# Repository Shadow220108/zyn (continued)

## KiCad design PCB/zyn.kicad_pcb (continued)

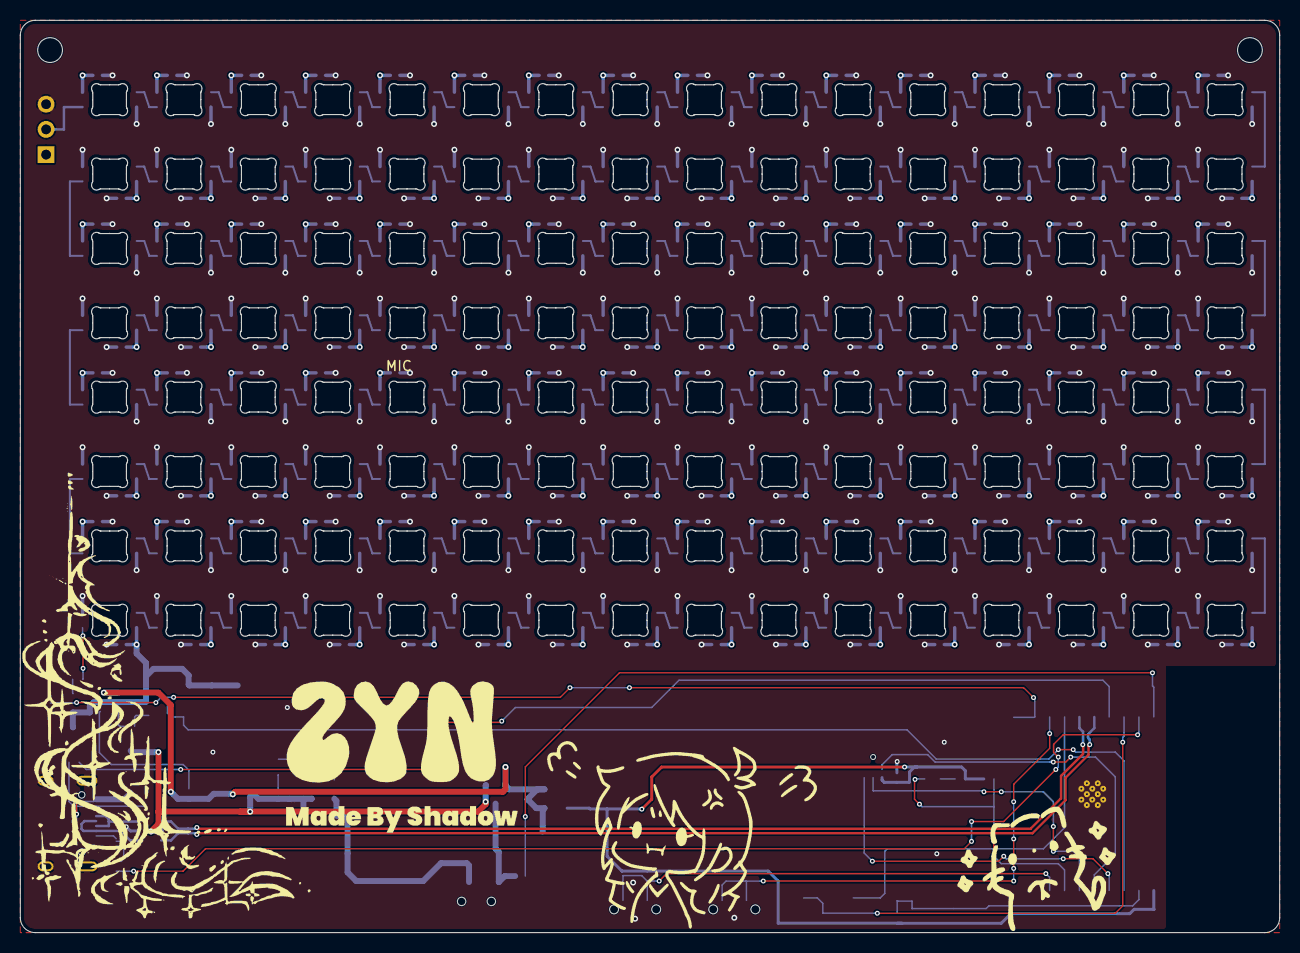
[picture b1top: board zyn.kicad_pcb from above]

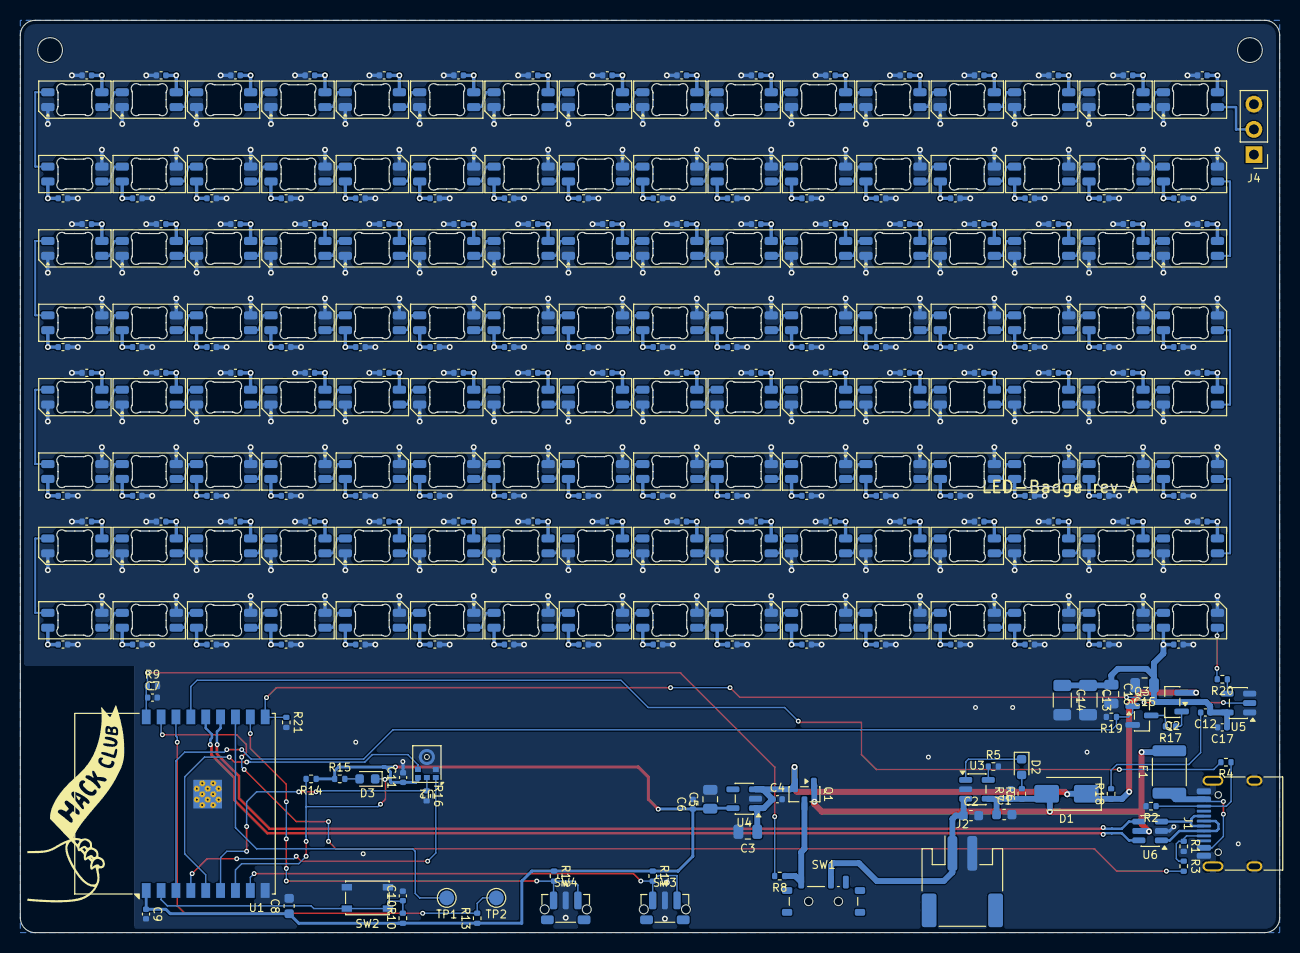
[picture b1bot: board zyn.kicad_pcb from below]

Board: 4 copper layers, 127.0 x 92.0 mm, 318 parts (316 on the bottom side), 165 nets.

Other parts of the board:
H1, H2: MountingHole_2.5mm

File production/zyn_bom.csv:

Designator,Footprint,Quantity,Value,LCSC Part #
"C1, C2",0603,2,4.7u/10V,CL10A475KO8NNNC
"C10, C4, C6",0402,3,1u/10V,CL05A105KP5NNNC
"C101, C102, C103, C104, C105, C106, C107, C108, C109, C11, C110, C111, C112, C113, C114, C115, C116, C117, C118, C119, C120, C121, C122, C123, C124, C125, C126, C127, C128, C129, C130, C131, C132, C133, C134, C135, C136, C137, C138, C139, C140, C141, C142, C143, C144, C145, C146, C147, C148, C149, C150, C151, C152, C153, C154, C155, C156, C157, C158, C159, C160, C161, C162, C163, C164, C165, C166, C167, C168, C169, C17, C170, C171, C172, C173, C174, C175, C176, C177, C178, C179, C180, C181, C182, C183, C184, C185, C186, C187, C188, C189, C190, C191, C192, C193, C194, C195, C196, C197, C198, C199, C200, C201, C202, C203, C204, C205, C206, C207, C208, C209, C210, C211, C212, C213, C214, C215, C216, C217, C218, C219, C220, C221, C222, C223, C224, C225, C226, C227, C228, C7, C9",0402,132,100n/16V,CL05B104KO5NNNC
C12,0402,1,47n/16V,CL05B473KO5NNNC
"C13, C14",1206,2,47u/10V,CL31A476MPHNNNE
"C15, C16, C3, C5",0805,4,22u/10V,CL21A226MPQNNNE
C8,0603,1,10u/10V,CL10A106KP8NNNC
D1,D_SMA,1,SS34,SS34 (3 A / 40 V)
"D101, D102, D103, D104, D105, D106, D107, D108, D109, D110, D111, D112, D113, D114, D115, D116, D117, D118, D119, D120, D121, D122, D123, D124, D125, D126, D127, D128, D129, D130, D131, D132, D133, D134, D135, D136, D137, D138, D139, D140, D141, D142, D143, D144, D145, D146, D147, D148, D149, D150, D151, D152, D153, D154, D155, D156, D157, D158, D159, D160, D161, D162, D163, D164, D165, D166, D167, D168, D169, D170, D171, D172, D173, D174, D175, D176, D177, D178, D179, D180, D181, D182, D183, D184, D185, D186, D187, D188, D189, D190, D191, D192, D193, D194, D195, D196, D197, D198, D199, D200, D201, D202, D203, D204, D205, D206, D207, D208, D209, D210, D211, D212, D213, D214, D215, D216, D217, D218, D219, D220, D221, D222, D223, D224, D225, D226, D227, D228",LED_SK6812MINI-E_3.2x2.8mm_P1.5mm_ReverseMount,128,SK6812MINI-E,SK6812MINI-E
D2,0603,1,RED (charging),KT-0603R
D3,0603,1,BLUE (IO8),KT-0603B
F1,1812,1,2A,"Bourns MF-MSMF200-2 (1812, 2 A hold)"
J1,USB_C_Receptacle_HRO_TYPE-C-31-M-12,1,USB-C,HRO TYPE-C-31-M-12
J2,JST_PH_S2B-PH-SM4-TB_1x02-1MP_P2.00mm_Horizontal,1,LiPo 1S (JST-PH),JST S2B-PH-SM4-TB
J4,PinHeader_1x03_P2.54mm_Vertical,1,CHAIN OUT,2.54 mm 1x3 header (DNP)
"Q1, Q2",SOT-23,2,AO3401A,AO3401A
Q3,SOT-23,1,2N7002,2N7002
"R1, R2",0402,2,5.1k,RC0402FR-075K1L
"R10, R11, R12, R13, R14, R17, R3, R4",0402,8,10k,RC0402FR-0710KL
"R15, R6",0402,2,1k,RC0402FR-071KL
"R16, R18, R19, R21, R7, R8, R9",0402,7,100k,RC0402FR-07100KL
R20,0402,1,33R,RC0402FR-0733RL
R5,0402,1,2k,RC0402FR-072KL
SW1,SW_SPDT_Shouhan_MSK12C02,1,POWER (slide),Shouhan MSK12C02
SW2,SW_SPST_PTS810,1,RESET,C&K PTS810SJM250SMTRLFS
SW3,SW_Push_1P1T-MP_NO_Horizontal_Alps_SKRTLAE010,1,BTN_A / BOOT,Alps SKRTLAE010
SW4,SW_Push_1P1T-MP_NO_Horizontal_Alps_SKRTLAE010,1,BTN_B,Alps SKRTLAE010
U1,ESP32-C3-WROOM-02,1,ESP32-C3-WROOM-02,ESP32-C3-WROOM-02-N4
U2,InvenSense_ICS-43434-6_3.5x2.65mm,1,ICS-43434,ICS-43434
U3,SOT-23-5,1,MCP73831-2-OT,MCP73831T-2ACI/OT
U4,SOT-23-5,1,AP2112K-3.3,AP2112K-3.3TRG1
U5,SOT-23-5,1,SN74LV1T125DBV,SN74LV1T125DBVR
U6,SOT-23-6,1,USBLC6-2SC6,USBLC6-2SC6

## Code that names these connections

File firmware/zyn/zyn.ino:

/*
  zyn: 16 x 8 SK6812 mini-e matrix on an ESP32-C3 (Arduino IDE, Espressif ESP32 core)

  written with help from AI. the pins were checked against the netlist and the
  ESP32-C3-WROOM-02 pin layout, but this exact file has not been run on the board yet.

  needs the FastLED library (Library Manager, "FastLED").

  buttons
  - BTN_A (IO9, the boot button): cycle effects
  - BTN_B (RXD / GPIO20): cycle brightness

  the mic (ICS-43434) is not used in this version.
*/

#include <FastLED.h>

const uint8_t LED_DATA_PIN = 10;   // IO10 -> LED_DATA -> level shifter -> first pixel DIN
const uint8_t LED_EN_PIN   = 4;    // IO4 -> LED_EN, HIGH turns VLED on for the matrix
const uint8_t BTN_A_PIN    = 9;    // IO9 (boot), active low
const uint8_t BTN_B_PIN    = 20;   // RXD / GPIO20, BTN_B, active low
const uint8_t STATUS_PIN   = 8;    // IO8 -> blue status LED (D3)

const uint8_t COLS = 16;
const uint8_t ROWS = 8;
const uint16_t NUM_LEDS = COLS * ROWS;  // 128

// the power rail for the matrix is VSYS, so on battery the pixels see 3.0 to 4.2 V.
// keep the brightness low until you have checked the pixels at that voltage.
const uint8_t BRIGHT[] = {10, 25, 50};

CRGB leds[NUM_LEDS];
uint8_t mode = 0;          // 0 rainbow, 1 scan line, 2 sparkle, 3 breathe
uint8_t brightLevel = 0;

// the pixels are chained DIN to DOUT in a snake: row 0 runs left to right,
// row 1 runs right to left, and so on. this gives the index in the chain for (x, y).
uint16_t xyToIndex(uint8_t x, uint8_t y) {
  uint8_t col = (y % 2 == 0) ? x : (COLS - 1 - x);
  return y * COLS + col;
}

void effectRainbow(uint32_t t) {
  for (uint8_t y = 0; y < ROWS; y++)
    for (uint8_t x = 0; x < COLS; x++)
      leds[xyToIndex(x, y)] = CHSV((x * 8 + y * 16 + t / 20) & 0xFF, 255, 255);
}

void effectScan(uint32_t t) {
  fill_solid(leds, NUM_LEDS, CRGB::Black);
  uint8_t col = (t / 120) % COLS;
  for (uint8_t y = 0; y < ROWS; y++)
    leds[xyToIndex(col, y)] = CRGB::Cyan;
}

void effectSparkle() {
  fadeToBlackBy(leds, NUM_LEDS, 40);
  if (random8() < 90) leds[random16(NUM_LEDS)] = CHSV(random8(), 255, 255);
}

void effectBreathe(uint32_t t) {
  (void)t;
  uint8_t v = beatsin8(20, 0, 255);
  fill_solid(leds, NUM_LEDS, CHSV(160, 255, v));
}

// simple edge detect, polled every 20 ms
bool lastA = HIGH, lastB = HIGH;
void readButtons() {
  bool a = digitalRead(BTN_A_PIN);
  bool b = digitalRead(BTN_B_PIN);
  if (lastA == HIGH && a == LOW) mode = (mode + 1) % 4;
  if (lastB == HIGH && b == LOW) brightLevel = (brightLevel + 1) % 3;
  lastA = a;
  lastB = b;
}

void setup() {
  pinMode(LED_EN_PIN, OUTPUT);
  digitalWrite(LED_EN_PIN, HIGH);
  pinMode(BTN_A_PIN, INPUT_PULLUP);
  pinMode(BTN_B_PIN, INPUT_PULLUP);
  pinMode(STATUS_PIN, OUTPUT);

  FastLED.addLeds<SK6812, LED_DATA_PIN, GRB>(leds, NUM_LEDS);
  FastLED.setMaxPowerInVoltsAndMilliamps(3.7, 400);
  FastLED.setBrightness(BRIGHT[brightLevel]);
}

void loop() {
  static uint32_t lastPoll = 0, lastFrame = 0;
  uint32_t t = millis();

  if (t - lastPoll >= 20) {
    lastPoll = t;
    readButtons();
  }

  if (t - lastFrame >= 33) {
    lastFrame = t;
    switch (mode) {
      case 0: effectRainbow(t); break;
      case 1: effectScan(t); break;
      case 2: effectSparkle(); break;
      case 3: effectBreathe(t); break;
    }
    FastLED.setBrightness(BRIGHT[brightLevel]);
    FastLED.show();
    digitalWrite(STATUS_PIN, (t / 500) & 1);  // heartbeat blink
  }
}
